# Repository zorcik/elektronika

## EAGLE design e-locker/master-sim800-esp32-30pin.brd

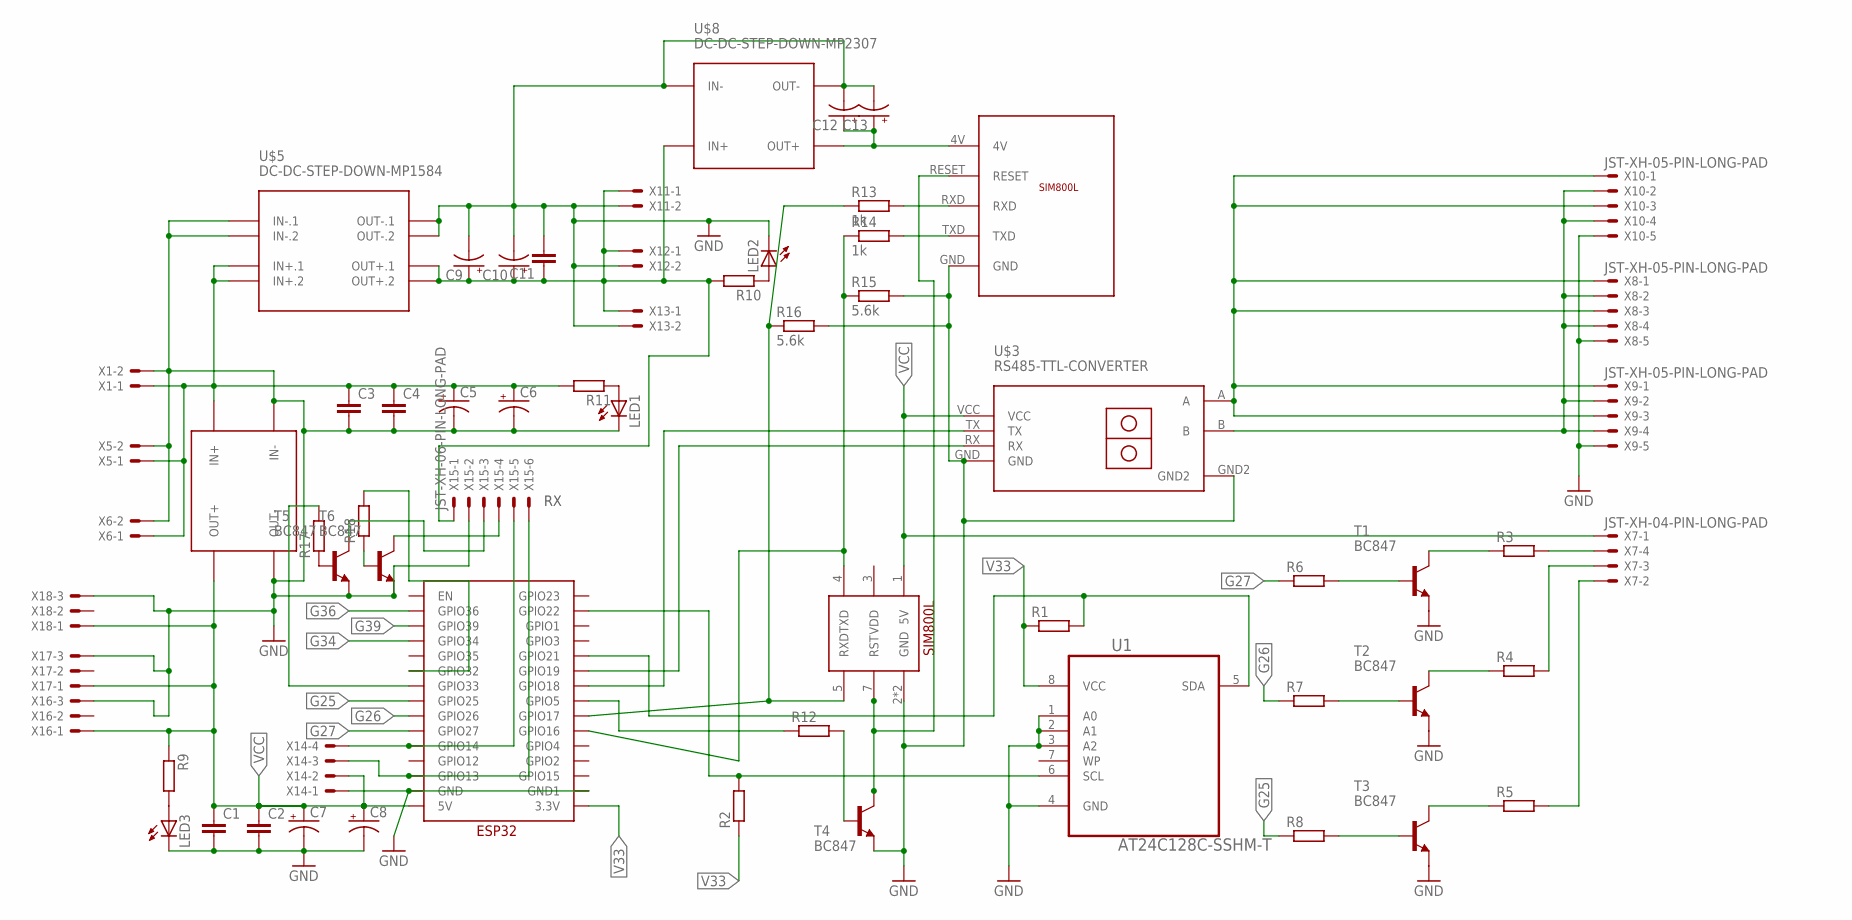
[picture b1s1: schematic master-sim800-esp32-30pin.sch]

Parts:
C1, C2, C3, C4, C11: C; C0805
C5, C6, C7, C8, C12, C13: CPOL-USE5-8.5; E5-8,5
C9, C10: CPOL-USE5-6; E5-6
LED1, LED2, LED3: LEDCHIPLED_1206; CHIPLED_1206
R1, R2, R3, R4, R5, R6, R7, R8, R9, R10, R11, R12, R17, R18: RR1206; R1206
R13, R14: 1k; R1206
R15, R16: 5.6k; R1206
T1, T2, T3, T4, T5, T6: BC847; SOT23
U1: AT24C128C-SSHM-T; SOIC127P600X175-8N
U$1: ESP32-30PIN
U$2: SIM800L; SIP
U$3: RS485-TTL-CONVERTER
U$4, U$8: DC-DC-STEP-DOWN-MP2307
U$5: DC-DC-STEP-DOWN-MP1584
U$7: SIM800L-V1; SIM800L
X1, X5, X6, X11, X12, X13: JST-XH-02-PIN-LONG-PAD; JST-XH-02-PACKAGE-LONG-PAD
X7, X14: JST-XH-04-PIN-LONG-PAD; JST-XH-04-PACKAGE-LONG-PAD
X8, X9, X10: JST-XH-05-PIN-LONG-PAD; JST-XH-05-PACKAGE-LONG-PAD
X15: JST-XH-06-PIN-LONG-PAD; JST-XH-06-PACKAGE-LONG-PAD
X16, X17, X18: JST-XH-03-PIN-LONG-PAD; JST-XH-03-PACKAGE-LONG-PAD

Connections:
G25: R8.1, U$1.GPIO25
G26: R7.1, U$1.GPIO26
G27: R6.1, U$1.GPIO27
G34: U$1.GPIO34
G36: U$1.GPIO36
G39: U$1.GPIO39
GND: C1.2, C2.2, C3.2, C4.2, C5.-, C6.-, C7.-, C8.-, C9.-, C10.-, C11.2, C12.-, C13.-, LED1.C, LED2.C, LED3.C, R15.2, R16.2, T1.2 (E), T2.2 (E), T3.2 (E), T4.2 (E), T5.2 (E), T6.2 (E), U1.1 (A0), U1.2 (A1), U1.3 (A2), U1.4 (GND), U$1.GND, U$1.GND1, U$2.2 (GND), U$2.6 (GND), U$3.GND, U$3.GND2, U$4.IN-, U$4.OUT-, U$5.IN-.1, U$5.IN-.2, U$5.OUT-.1, U$5.OUT-.2, U$7.GND, U$8.IN-, U$8.OUT-, X1.2, X5.2, X6.2, X8.5, X9.5, X10.5, X11.2, X12.2, X13.2, X14.1, X15.2, X16.3, X17.3, X18.3
unnamed: C3.1, C4.1, C5.+, C6.+, R11.2, U$4.IN+, U$5.IN+.1, U$5.IN+.2, X1.1, X5.1, X6.1
unnamed: R2.2, U1.6 (SCL), U$1.GPIO22
unnamed: R14.1, R15.1, U$1.GPIO16, U$2.4 (TXD)
unnamed: R13.1, R16.1, U$1.GPIO17, U$2.5 (RXD)
unnamed: U$3.A, X8.1, X8.3, X9.1, X9.3, X10.1, X10.3
unnamed: U$1.GPIO18, U$3.TX
unnamed: U$1.GPIO19, U$3.RX
unnamed: R1.2, U1.5 (SDA), U$1.GPIO21
unnamed: R3.1, T1.3 (C)
unnamed: R4.1, T2.3 (C)
unnamed: R5.1, T3.3 (C)
unnamed: R3.2, X7.4
unnamed: R4.2, X7.3
unnamed: R5.2, X7.2
unnamed: R6.2, T1.1 (B)
unnamed: R7.2, T2.1 (B)
unnamed: R8.2, T3.1 (B)
unnamed: T4.3 (C), U$2.7 (RST), U$7.RESET
unnamed: U$3.B, X8.2, X8.4, X9.2, X9.4, X10.2, X10.4
unnamed: LED3.A, R9.2
unnamed: LED2.A, R10.1
unnamed: LED1.A, R11.1
unnamed: C9.+, C10.+, C11.1, R10.2, U$5.OUT+.1, U$5.OUT+.2, U$8.IN+, X11.1, X12.1, X13.1, X15.1
unnamed: R12.1, U$1.GPIO5
unnamed: R12.2, T4.1 (B)
unnamed: R13.2, U$7.RXD
unnamed: R14.2, U$7.TXD
unnamed: C12.+, C13.+, U$7.4V, U$8.OUT+
unnamed: U$1.GPIO13, X14.3, X15.6
unnamed: U$1.GPIO14, X14.4, X15.5
unnamed: R17.1, T5.1 (B)
unnamed: R18.1, T6.1 (B)
unnamed: R18.2, U$1.GPIO32
unnamed: T6.3 (C), X15.4
unnamed: T5.3 (C), X15.3
unnamed: R17.2, U$1.GPIO33
V33: R1.1, R2.1, U1.8 (VCC), U$1.3.3V
VCC: C1.1, C2.1, C7.+, C8.+, R9.1, U$1.5V, U$2.1 (5V), U$3.VCC, U$4.OUT+, X7.1, X14.2, X16.1, X17.1, X18.1

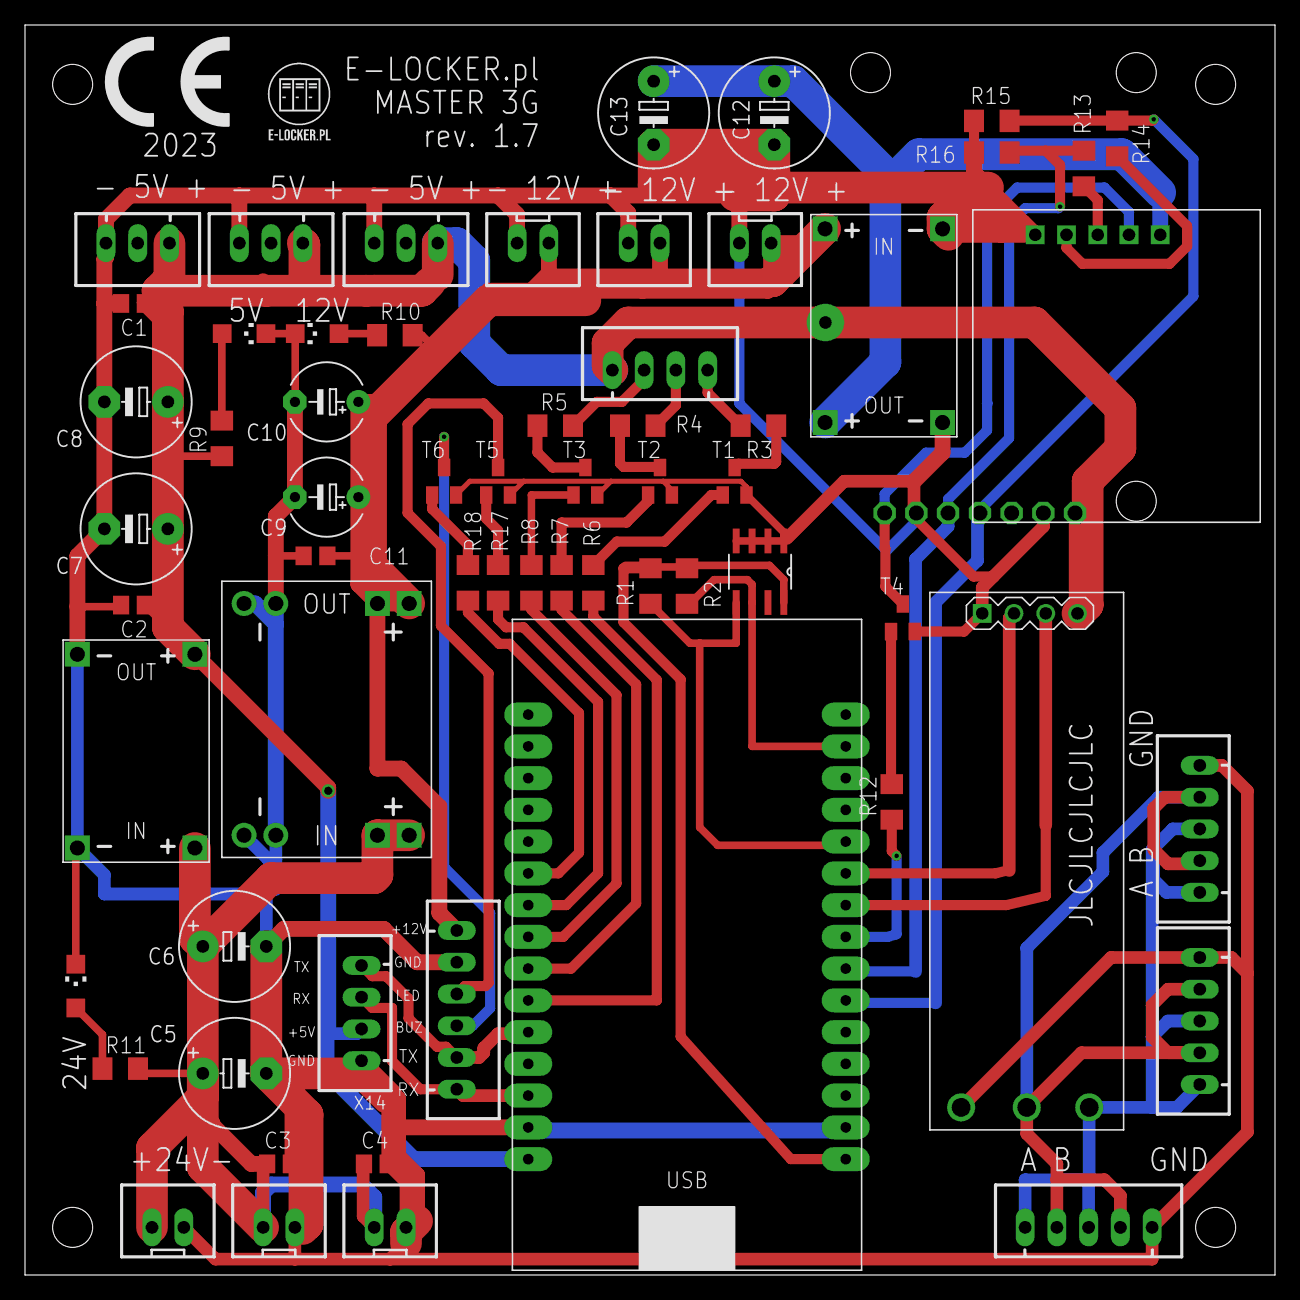
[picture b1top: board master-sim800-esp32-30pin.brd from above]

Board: 2 copper layers, 100.0 x 100.0 mm, 65 parts (0 on the bottom side), 42 nets.

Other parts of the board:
U$6: ELOCKER
U$9: CE_7.3MM

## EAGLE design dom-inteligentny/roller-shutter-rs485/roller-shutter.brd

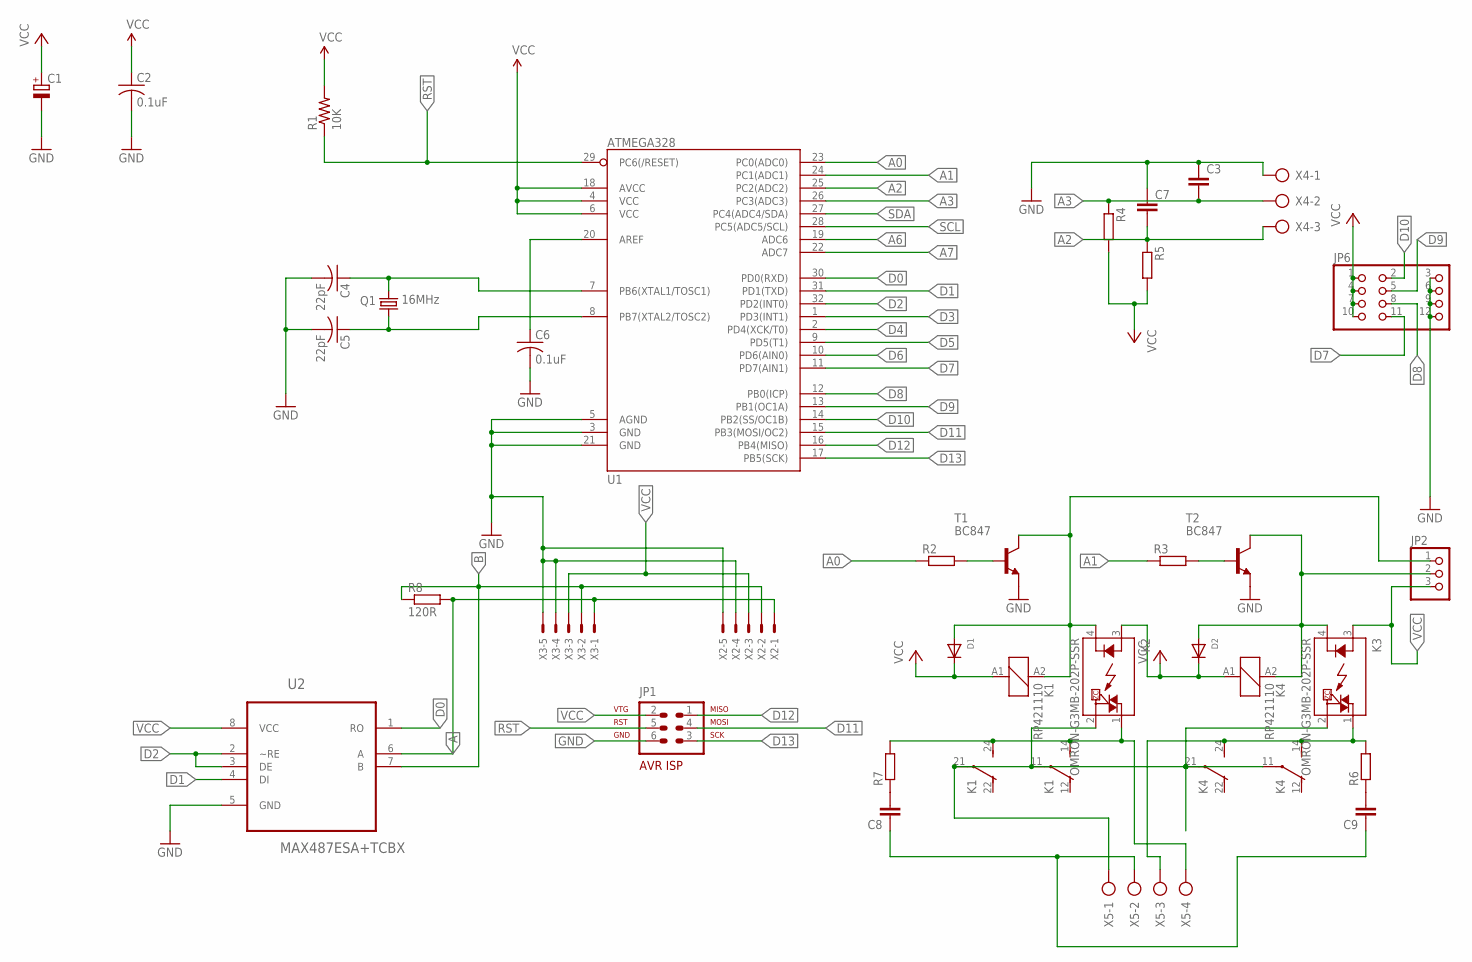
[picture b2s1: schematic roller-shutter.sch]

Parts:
C1: CPOL-EUSANYO_SMD_C6; SANYO-OSCON_SMD_C6
C2, C6: 0.1uF; C0805
C3, C7: C; C0805
C4, C5: 22pF; C1206
C8, C9: CC1812; C1812
D1, D2: DIODE_SOD-123FL; SOD-123FL
JP1: AVR-ISP-6
JP2: PINHD-1X3; 1X03
JP6: PINHD-3X4; 3X04
K1, K4: RP421110; RP420
K2, K3: OMRON-G3MB-202P-SSR
Q1: 16MHz; HC49/S
R1: 10K; R1206
R2, R3, R4, R5: RR1206; R1206
R6, R7: RR2512; R2512
R8: 120R; R0603
T1, T2: BC847; SOT23
U1: ATMEGA328; TQFP32-08
U2: MAX487ESA+TCBX; SOIC127P600X175-8N
X2, X3: JST-XH-05-PIN-LONG-PAD; JST-XH-05-PACKAGE-LONG-PAD
X4: AK500/3
X5: AK500/4

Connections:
A: R8.2, U2.6 (A), X2.1, X3.1
A0: R2.1, U1.23 (PC0(ADC0))
A1: R3.1, U1.24 (PC1(ADC1))
A2: C7.2, R5.1, U1.25 (PC2(ADC2)), X4.3
A3: C3.2, R4.1, U1.26 (PC3(ADC3)), X4.2
A6: U1.19 (ADC6)
A7: U1.22 (ADC7)
AREF: C6.1, U1.20 (AREF)
B: R8.1, U2.7 (B), X2.2, X3.2
D0: U1.30 (PD0(RXD)), U2.1 (RO)
D1: U1.31 (PD1(TXD)), U2.4 (DI)
D2: U1.32 (PD2(INT0)), U2.2 (~RE), U2.3 (DE)
D3: U1.1 (PD3(INT1))
D4: U1.2 (PD4(XCK/T0))
D5: U1.9 (PD5(T1))
D6: U1.10 (PD6(AIN0))
D7: JP6.11, U1.11 (PD7(AIN1))
D8: JP6.8, U1.12 (PB0(ICP))
D9: JP6.5, U1.13 (PB1(OC1A))
D10: JP6.2, U1.14 (PB2(SS/OC1B))
D11: JP1.4, U1.15 (PB3(MOSI/OC2))
D12: JP1.1, U1.16 (PB4(MISO))
D13: JP1.3, U1.17 (PB5(SCK))
GND: C1.-, C2.2, C3.1, C4.2, C5.2, C6.2, C7.1, JP1.6, JP6.3, JP6.6, JP6.9, JP6.12, T1.2 (E), T2.2 (E), U1.3 (GND), U1.5 (AGND), U1.21 (GND), U2.5 (GND), X2.4, X2.5, X3.4, X3.5, X4.1
unnamed: D1.A, JP2.1, K1.A2 (1), K2.4 (K), T1.3 (C)
unnamed: D2.A, JP2.2, K3.4 (K), K4.A2 (1), T2.3 (C)
unnamed: K1.11, K1.21, K2.2 (DS2), K3.2 (DS2), K4.11, K4.21, X5.1
unnamed: R2.2, T1.1 (B)
unnamed: R3.2, T2.1 (B)
unnamed: K1.14 (S), K1.24 (S), K2.1 (DS1), R7.2, X5.4
unnamed: K3.1 (DS1), K4.14 (S), K4.24 (S), R6.2, X5.3
unnamed: C8.2, R7.1
unnamed: C9.2, R6.1
unnamed: C8.1, C9.1, X5.2
unnamed: C4.1, Q1.2, U1.7 (PB6(XTAL1/TOSC1))
unnamed: C5.1, Q1.1, U1.8 (PB7(XTAL2/TOSC2))
RST: JP1.5, R1.1, U1.29 (PC6(/RESET))
SCL: U1.28 (PC5(ADC5/SCL))
SDA: U1.27 (PC4(ADC4/SDA))
VCC: C1.+, C2.1, D1.C, D2.C, JP1.2, JP2.3, JP6.1, JP6.4, JP6.7, JP6.10, K1.A1 (2), K2.3 (A), K3.3 (A), K4.A1 (2), R1.2, R4.2, R5.2, U1.4 (VCC), U1.6 (VCC), U1.18 (AVCC), U2.8 (VCC), X2.3, X3.3

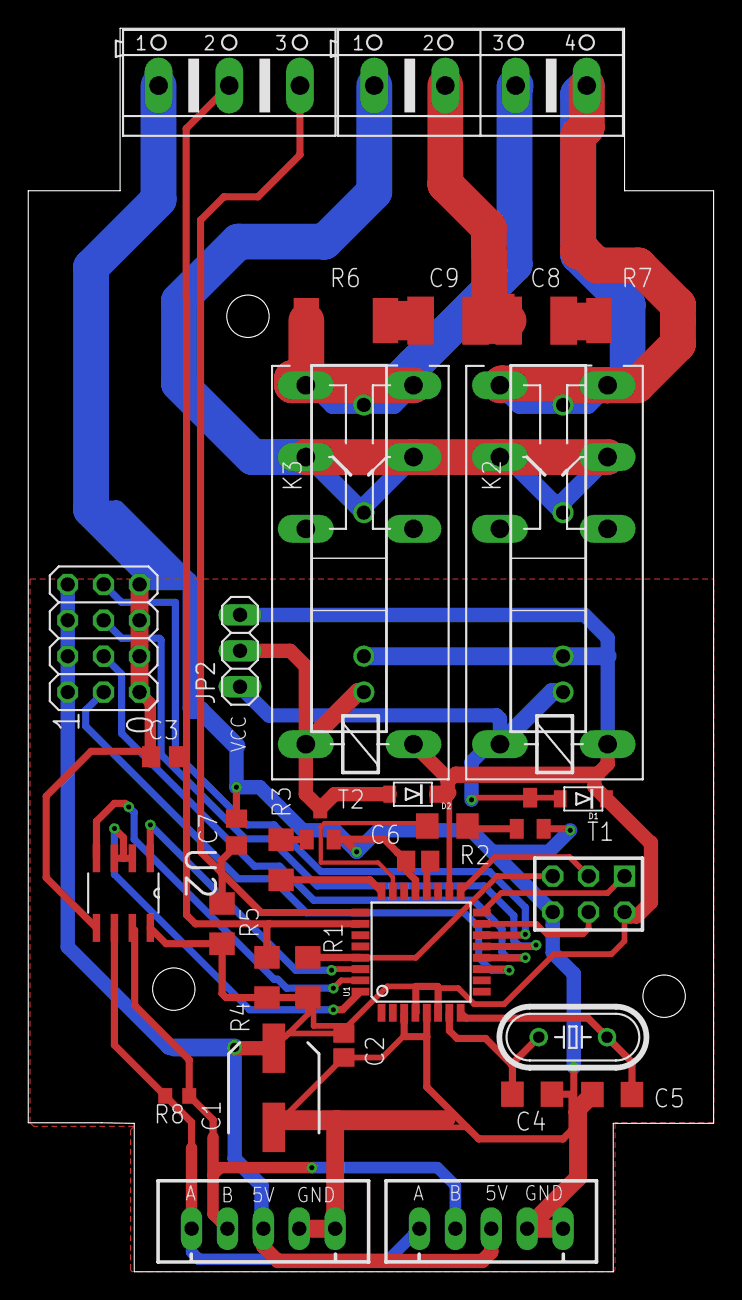
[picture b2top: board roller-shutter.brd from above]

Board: 2 copper layers, 48.5 x 88.0 mm, 35 parts (0 on the bottom side), 32 nets.

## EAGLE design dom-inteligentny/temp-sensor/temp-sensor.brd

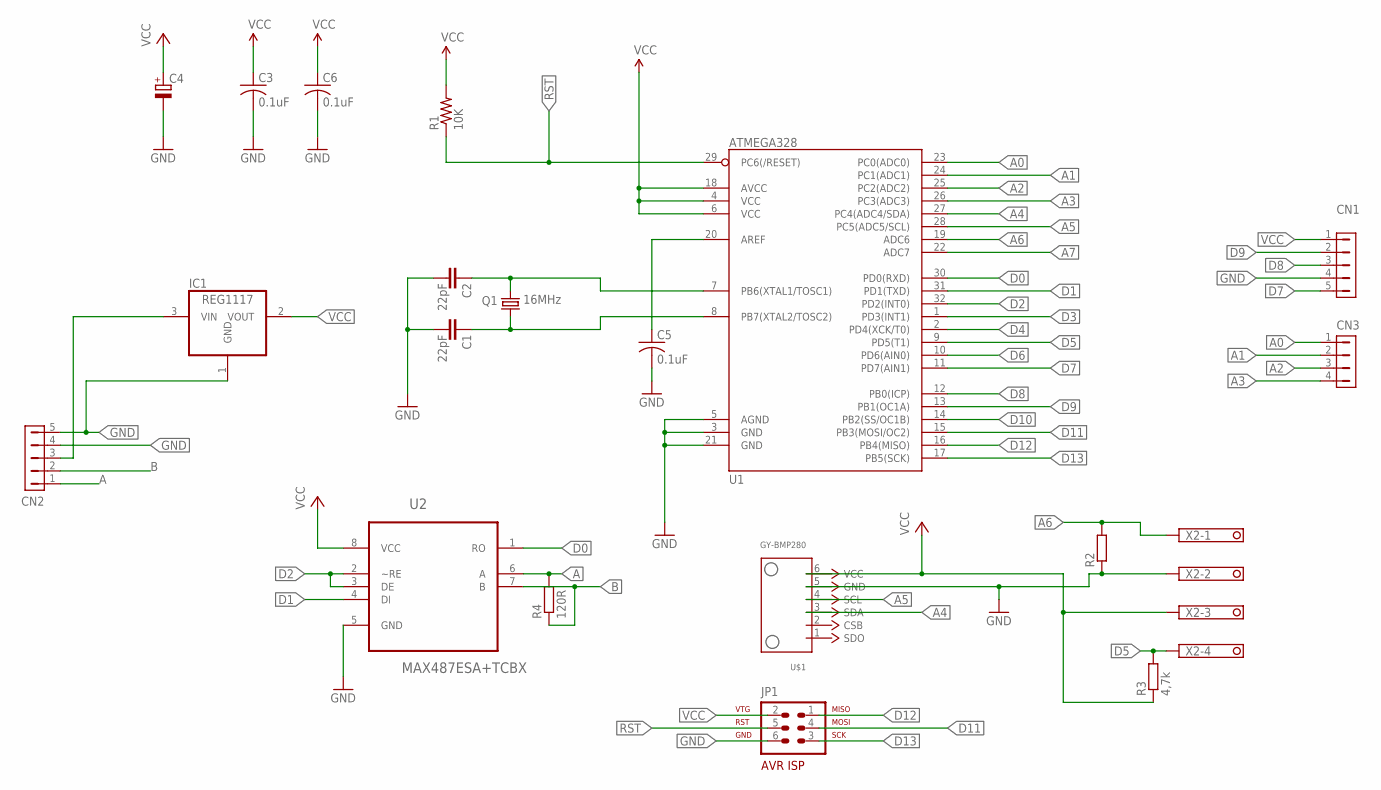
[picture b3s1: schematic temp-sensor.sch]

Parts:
C1, C2: 22pF; C0805
C3, C5, C6: 0.1uF; C0805
C4: CPOL-EUSANYO_SMD_C6; SANYO-OSCON_SMD_C6
CN1, CN2: HDR-1X5-SIP-100; SIP-100-5V
CN3: HDR-1X4-SIP-100; SIP-100-4V
IC1: REG1117; SOT223
JP1: AVR-ISP-6
Q1: 16MHz; HC49/S
R1: 10K; R1206
R2: RR1206; R1206
R3: 4,7k; R1206
R4: 120R; R0603
U1: ATMEGA328; TQFP32-08
U2: MAX487ESA+TCBX; SOIC127P600X175-8N
U$1: GY-BMP280
X2: TERMINAL-BLOCK-3.5MM-4-PIN-LONG-PAD; TERMINAL-BLOCK-4-PIN-3.5MM-LONG-PAD

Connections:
A: CN2.1, R4.2, U2.6 (A)
A0: CN3.1, U1.23 (PC0(ADC0))
A1: CN3.2, U1.24 (PC1(ADC1))
A2: CN3.3, U1.25 (PC2(ADC2))
A3: CN3.4, U1.26 (PC3(ADC3))
A4: U1.27 (PC4(ADC4/SDA)), U$1.3 (SDA)
A5: U1.28 (PC5(ADC5/SCL)), U$1.4 (SCL)
A6: R2.2, U1.19 (ADC6), X2.1
A7: U1.22 (ADC7)
AREF: C5.1, U1.20 (AREF)
B: CN2.2, R4.1, U2.7 (B)
D0: U1.30 (PD0(RXD)), U2.1 (RO)
D1: U1.31 (PD1(TXD)), U2.4 (DI)
D2: U1.32 (PD2(INT0)), U2.2 (~RE), U2.3 (DE)
D3: U1.1 (PD3(INT1))
D4: U1.2 (PD4(XCK/T0))
D5: R3.2, U1.9 (PD5(T1)), X2.4
D6: U1.10 (PD6(AIN0))
D7: CN1.5, U1.11 (PD7(AIN1))
D8: CN1.3, U1.12 (PB0(ICP))
D9: CN1.2, U1.13 (PB1(OC1A))
D10: U1.14 (PB2(SS/OC1B))
D11: JP1.4, U1.15 (PB3(MOSI/OC2))
D12: JP1.1, U1.16 (PB4(MISO))
D13: JP1.3, U1.17 (PB5(SCK))
GND: C1.2, C2.2, C3.2, C4.-, C5.2, C6.2, CN1.4, CN2.4, CN2.5, IC1.1 (GND), JP1.6, R2.1, U1.3 (GND), U1.5 (AGND), U1.21 (GND), U2.5 (GND), U$1.5 (GND), X2.2
unnamed: CN2.3, IC1.3 (VIN)
unnamed: C2.1, Q1.2, U1.7 (PB6(XTAL1/TOSC1))
unnamed: C1.1, Q1.1, U1.8 (PB7(XTAL2/TOSC2))
RST: JP1.5, R1.1, U1.29 (PC6(/RESET))
VCC: C3.1, C4.+, C6.1, CN1.1, IC1.2 (VOUT), JP1.2, R1.2, R3.1, U1.4 (VCC), U1.6 (VCC), U1.18 (AVCC), U2.8 (VCC), U$1.6 (VCC), X2.3

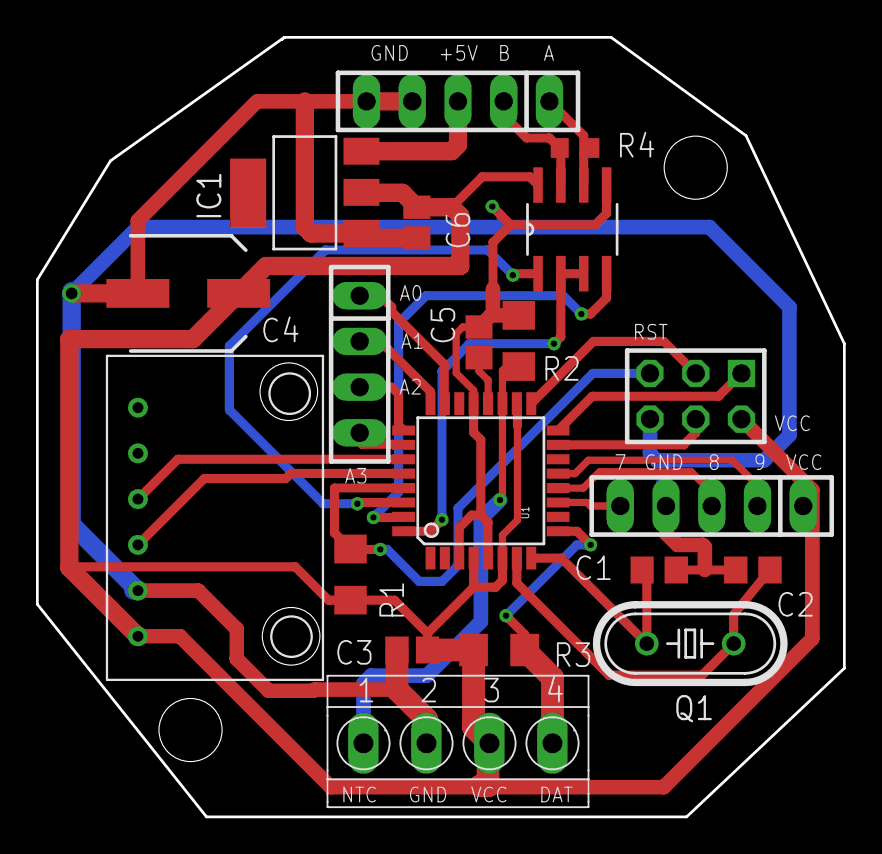
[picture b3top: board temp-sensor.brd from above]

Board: 2 copper layers, 44.8 x 43.3 mm, 20 parts (0 on the bottom side), 26 nets.

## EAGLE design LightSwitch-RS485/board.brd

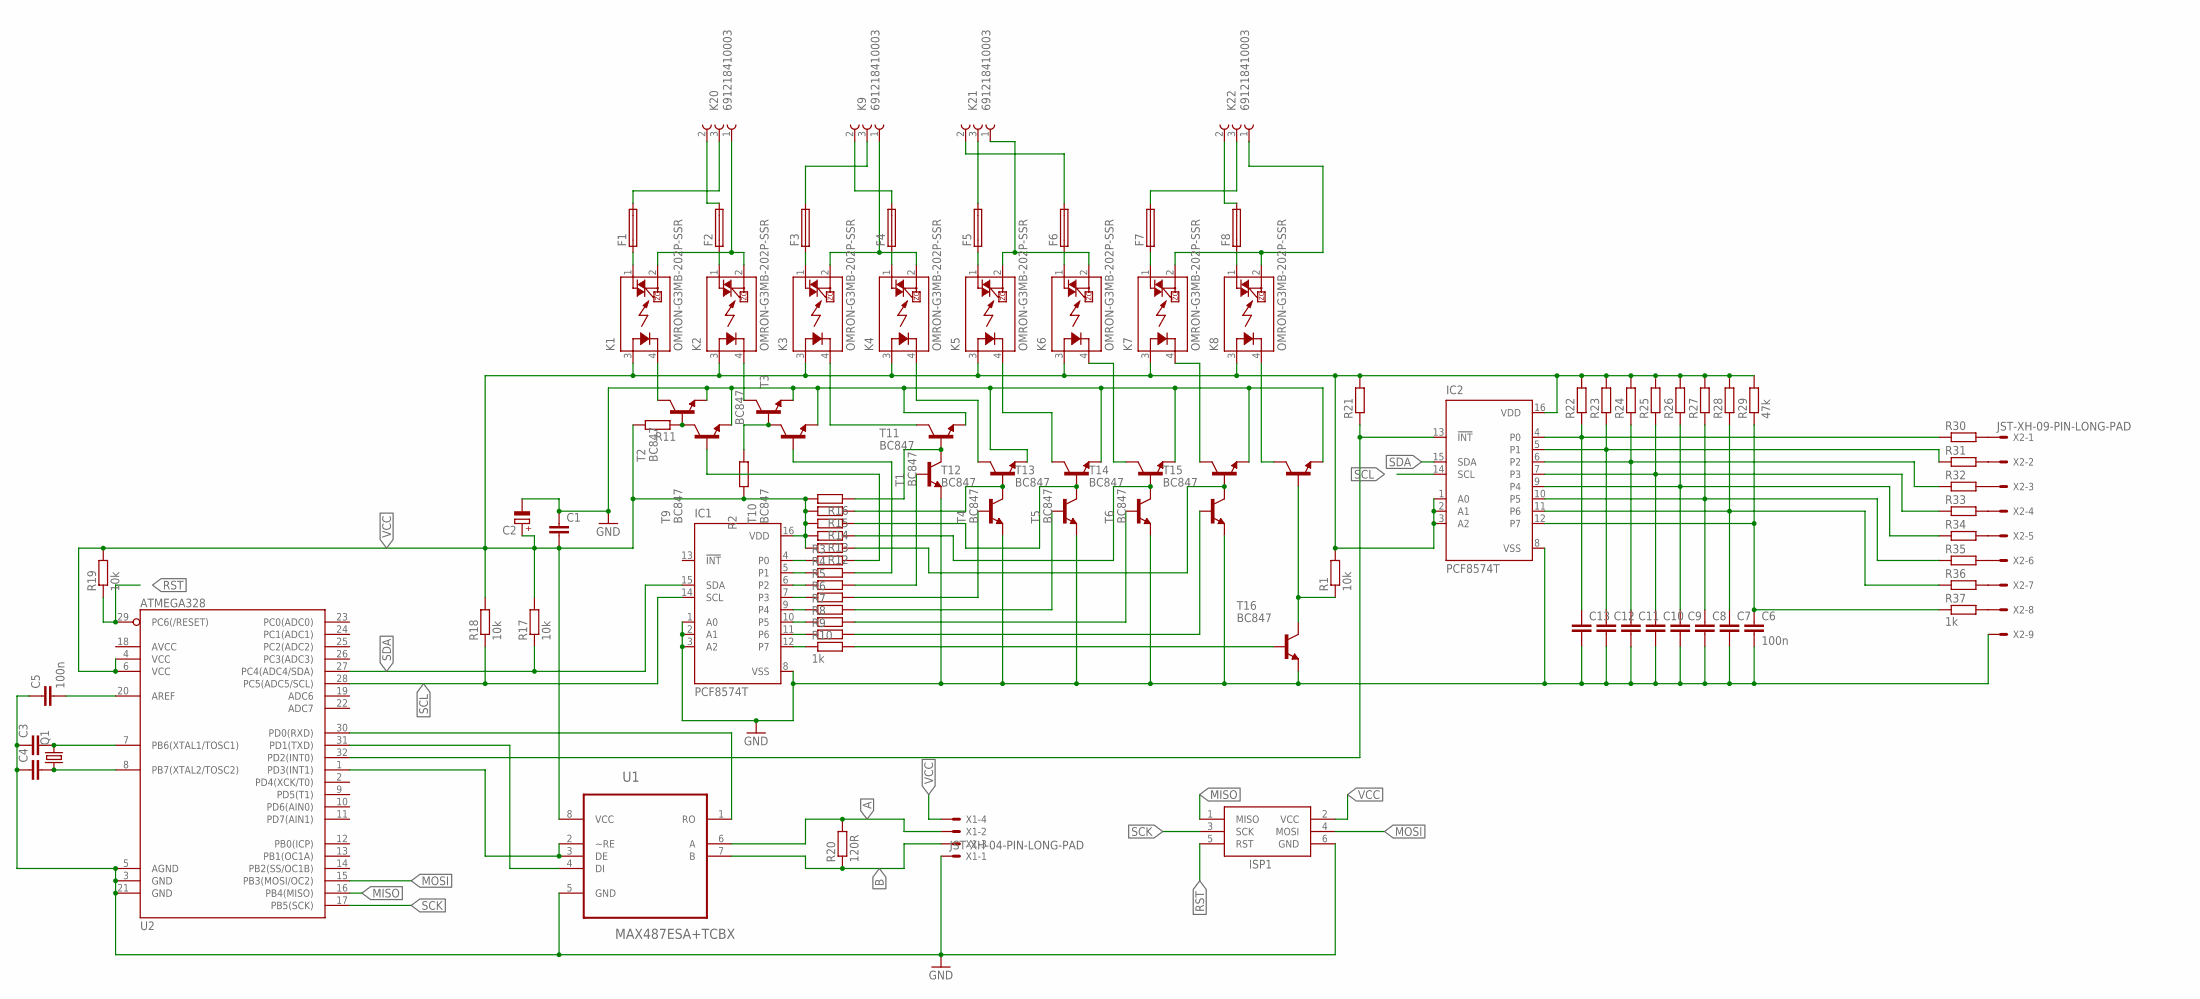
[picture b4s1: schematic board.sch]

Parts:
C1: CC1206; C1206
C2: CPOL-EU150CLZ-0810; 150CLZ-0810
C3, C4, C7, C8, C9, C10, C11, C12, C13: C; C0805
C5, C6: 100n; C0805
F1, F2, F3, F4, F5, F6, F7, F8: FUSELITTLEFUSE; LITTLEFUSE
IC1, IC2: PCF8574T; SO16W
ISP1: AVRISP-6; AVRISP
K1, K2, K3, K4, K5, K6, K7, K8: OMRON-G3MB-202P-SSR
K9, K20, K21, K22: 691218410003
Q1: CRYSTALHC49S; HC49/S
R1, R17, R18, R19: 10k; R1206
R2, R3, R4, R5, R6, R7, R8, R9, R11, R12, R13, R14, R15, R16, R21, R22, R23, R24, R25, R26, R27, R28, R30, R31, R32, R33, R34, R35, R36: RR1206; R1206
R10, R37: 1k; R1206
R20: 120R; R1206
R29: 47k; R1206
T1, T2, T3, T4, T5, T6, T7, T8, T9, T10, T11, T12, T13, T14, T15, T16: BC847; SOT23
U1: MAX487ESA+TCBX; SOIC127P600X175-8N
U2: ATMEGA328; TQFP32-08
X1: JST-XH-04-PIN-LONG-PAD; JST-XH-04-PACKAGE-LONG-PAD
X2: JST-XH-09-PIN-LONG-PAD; JST-XH-09-PACKAGE-LONG-PAD

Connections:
A: R20.2, U1.6 (A), X1.2
B: R20.1, U1.7 (B), X1.3
GND: C1.1, C2.-, C3.1, C4.1, C5.1, C6.2, C7.2, C8.2, C9.2, C10.2, C11.2, C12.2, C13.2, IC1.1 (A0), IC1.2 (A1), IC1.3 (A2), IC1.8 (VSS), IC2.8 (VSS), ISP1.6 (GND), T1.2 (E), T2.2 (E), T3.2 (E), T4.2 (E), T5.2 (E), T6.2 (E), T7.2 (E), T8.2 (E), T9.2 (E), T10.2 (E), T11.2 (E), T12.2 (E), T13.2 (E), T14.2 (E), T15.2 (E), T16.2 (E), U1.5 (GND), U2.3 (GND), U2.5 (AGND), U2.21 (GND), X1.1, X2.9
MISO: ISP1.1 (MISO), U2.16 (PB4(MISO))
MOSI: ISP1.4 (MOSI), U2.15 (PB3(MOSI/OC2))
unnamed: C13.1, IC2.4 (P0), R22.1, R30.1
unnamed: IC1.4 (P0), R3.1
unnamed: IC1.5 (P1), R4.1
unnamed: R1.1, T8.1 (B), T16.3 (C)
unnamed: IC1.6 (P2), R5.1
unnamed: IC1.7 (P3), R6.1
unnamed: IC1.9 (P4), R7.1
unnamed: IC1.10 (P5), R8.1
unnamed: IC1.11 (P6), R9.1
unnamed: IC1.12 (P7), R10.1
unnamed: U1.2 (~RE), U1.3 (DE), U2.1 (PD3(INT1))
unnamed: K7.4 (K), T7.3 (C)
unnamed: C3.2, Q1.2, U2.7 (PB6(XTAL1/TOSC1))
unnamed: C12.1, IC2.5 (P1), R23.1, R31.1
unnamed: C11.1, IC2.6 (P2), R24.1, R32.1
unnamed: C4.2, Q1.1, U2.8 (PB7(XTAL2/TOSC2))
unnamed: R10.2, T16.1 (B)
unnamed: C10.1, IC2.7 (P3), R25.1, R33.1
unnamed: K1.2 (DS2), K2.2 (DS2), K20.1 (3)
unnamed: C9.1, IC2.9 (P4), R26.1, R34.1
unnamed: C8.1, IC2.10 (P5), R27.1, R35.1
unnamed: C7.1, IC2.11 (P6), R28.1, R36.1
unnamed: C6.1, IC2.12 (P7), R29.1, R37.1
unnamed: R30.2, X2.1
unnamed: IC2.13 (!INT), R21.1, U2.32 (PD2(INT0))
unnamed: R31.2, X2.2
unnamed: R32.2, X2.3
unnamed: R33.2, X2.4
unnamed: R34.2, X2.5
unnamed: F1.1, K1.1 (DS1)
unnamed: F2.1, K2.1 (DS1)
unnamed: R35.2, X2.6
unnamed: F3.1, K3.1 (DS1)
unnamed: F4.1, K4.1 (DS1)
unnamed: R36.2, X2.7
unnamed: F5.1, K5.1 (DS1)
unnamed: K7.2 (DS2), K8.2 (DS2), K22.1 (3)
unnamed: F8.2, K22.2 (1)
unnamed: F7.2, K22.3 (2)
unnamed: F6.2, K21.2 (1)
unnamed: F5.2, K21.3 (2)
unnamed: F4.2, K9.2 (1)
unnamed: F3.2, K9.3 (2)
unnamed: F6.1, K6.1 (DS1)
unnamed: F1.2, K20.3 (2)
unnamed: F7.1, K7.1 (DS1)
unnamed: F8.1, K8.1 (DS1)
unnamed: R37.2, X2.8
unnamed: F2.2, K20.2 (1)
unnamed: R12.1, T7.1 (B), T15.3 (C)
unnamed: R14.1, T5.1 (B), T13.3 (C)
unnamed: C5.2, U2.20 (AREF)
unnamed: K3.2 (DS2), K4.2 (DS2), K9.1 (3)
unnamed: K5.2 (DS2), K6.2 (DS2), K21.1 (3)
unnamed: R13.1, T6.1 (B), T14.3 (C)
unnamed: U1.1 (RO), U2.30 (PD0(RXD))
unnamed: U1.4 (DI), U2.31 (PD1(TXD))
unnamed: R11.1, T2.1 (B), T9.3 (C)
unnamed: K1.4 (K), T2.3 (C)
unnamed: R2.2, T3.1 (B), T10.3 (C)
unnamed: K2.4 (K), T3.3 (C)
unnamed: R3.2, T9.1 (B)
unnamed: R4.2, T10.1 (B)
unnamed: R16.1, T1.1 (B), T11.3 (C)
unnamed: R15.1, T4.1 (B), T12.3 (C)
unnamed: R5.2, T11.1 (B)
unnamed: R6.2, T12.1 (B)
unnamed: K8.4 (K), T8.3 (C)
unnamed: R7.2, T13.1 (B)
unnamed: K6.4 (K), T6.3 (C)
unnamed: K5.4 (K), T5.3 (C)
unnamed: R8.2, T14.1 (B)
unnamed: K4.4 (K), T4.3 (C)
unnamed: R9.2, T15.1 (B)
unnamed: K3.4 (K), T1.3 (C)
RST: ISP1.5 (RST), R19.1, U2.29 (PC6(/RESET))
SCK: ISP1.3 (SCK), U2.17 (PB5(SCK))
SCL: IC1.14 (SCL), IC2.14 (SCL), R18.1, U2.28 (PC5(ADC5/SCL))
SDA: IC1.15 (SDA), IC2.15 (SDA), R17.1, U2.27 (PC4(ADC4/SDA))
VCC: C1.2, C2.+, IC1.16 (VDD), IC2.1 (A0), IC2.2 (A1), IC2.3 (A2), IC2.16 (VDD), ISP1.2 (VCC), K1.3 (A), K2.3 (A), K3.3 (A), K4.3 (A), K5.3 (A), K6.3 (A), K7.3 (A), K8.3 (A), R1.2, R2.1, R11.2, R12.2, R13.2, R14.2, R15.2, R16.2, R17.2, R18.2, R19.2, R21.2, R22.2, R23.2, R24.2, R25.2, R26.2, R27.2, R28.2, R29.2, U1.8 (VCC), U2.4 (VCC), U2.6 (VCC), X1.4

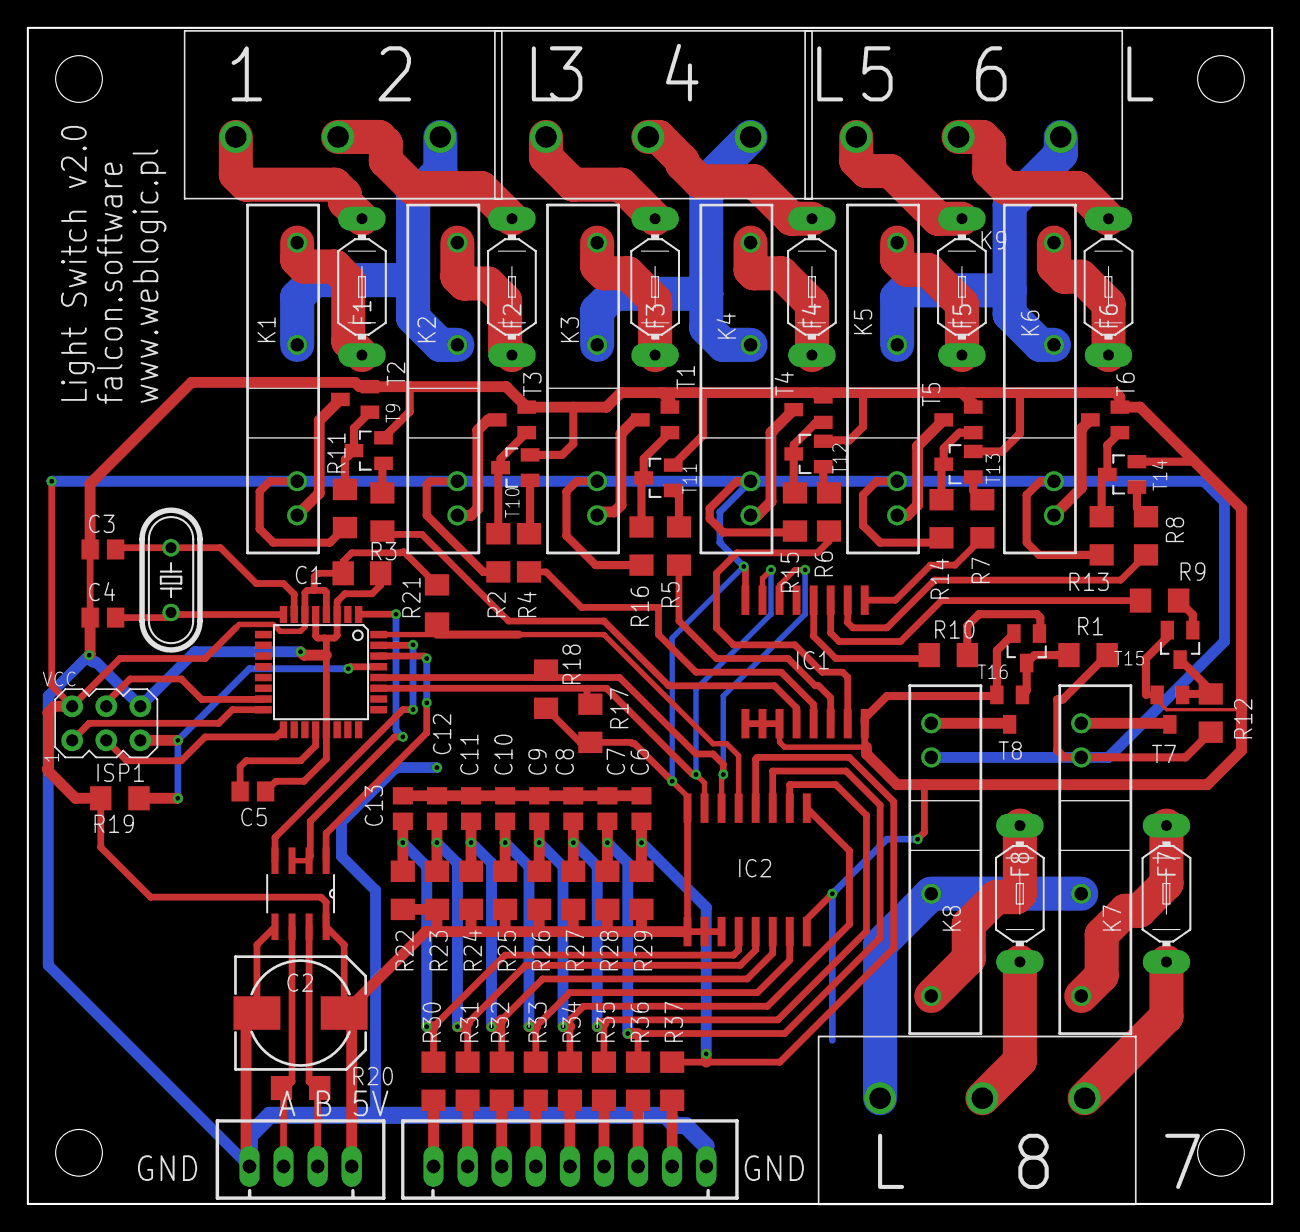
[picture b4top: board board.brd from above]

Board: 2 copper layers, 92.7 x 87.6 mm, 94 parts (0 on the bottom side), 85 nets.

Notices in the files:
parts and their libraries:
Wurth_Elektronik_Electromechanic_Termina: Copyright: Würth Elektronik
m-pad-2.1: License : GNU General Public License version 2 (see bottom)
SparkFun: Licensing: CC v3.0 Share-Alike You are welcome to use this library for commercial purposes.
